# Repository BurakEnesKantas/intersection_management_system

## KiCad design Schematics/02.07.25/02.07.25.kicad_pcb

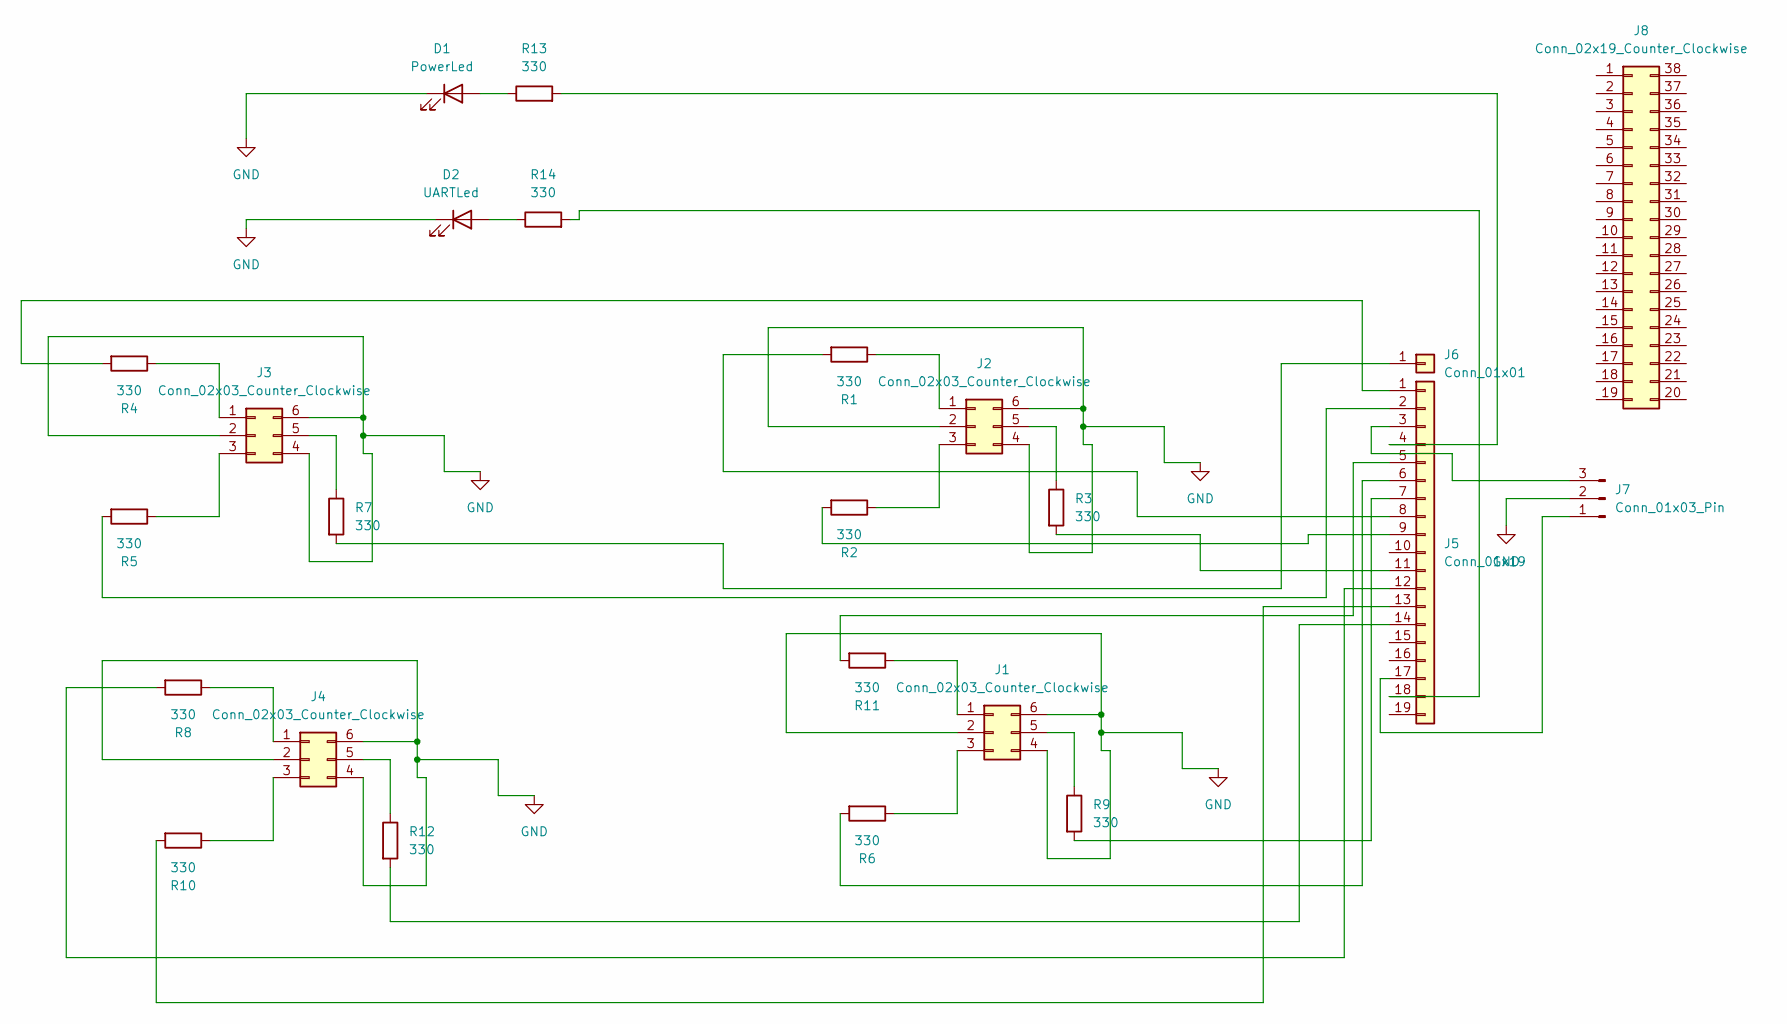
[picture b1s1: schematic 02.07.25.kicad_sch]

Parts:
D1: PowerLed; LED_D5.0mm
D2: UARTLed; LED_D5.0mm
J1, J2, J3, J4: Conn_02x03_Counter_Clockwise; PinSocket_2x03_P2.54mm_Vertical
J5: Conn_01x19; PinSocket_1x19_P2.54mm_Vertical
J6: Conn_01x01; PinSocket_1x01_P2.54mm_Vertical
J7: Conn_01x03_Pin; PinHeader_1x03_P2.54mm_Horizontal
J8: Conn_02x19_Counter_Clockwise; PinSocket_2x19_P2.54mm_Vertical
R1, R2, R3, R4, R5, R6, R7, R8, R9, R10, R11, R12, R13, R14: 330; R_Axial_DIN0207_L6.3mm_D2.5mm_P7.62mm_Horizontal

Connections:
GND: D1.1 (K), D2.1 (K), J1.2, J1.4, J1.6, J2.2, J2.4, J2.6, J3.2, J3.4, J3.6, J4.2, J4.4, J4.6, J7.2
unnamed: D1.2 (A), R13.1
unnamed: D2.2 (A), R14.1
unnamed: J1.1, R11.1
unnamed: J1.3, R6.1
unnamed: J1.5, R9.1
unnamed: J2.1, R1.1
unnamed: J2.3, R2.1
unnamed: J2.5, R3.1
unnamed: J3.1, R4.1
unnamed: J3.3, R5.1
unnamed: J3.5, R7.1
unnamed: J4.1, R8.1
unnamed: J4.3, R10.1
unnamed: J4.5, R12.1
unnamed: J5.1, R4.2
unnamed: J5.2, R5.2
unnamed: J5.3, J7.3
unnamed: J5.4, R13.2
unnamed: J5.5, R11.2
unnamed: J5.6, R6.2
unnamed: J5.7, R9.2
unnamed: J5.8, R1.2
unnamed: J5.9, R2.2
unnamed: J5.11, R3.2
unnamed: J5.12, R8.2
unnamed: J5.13, R10.2
unnamed: J5.14, R12.2
unnamed: J5.17, J7.1
unnamed: J5.18, R14.2
unnamed: J6.1, R7.2

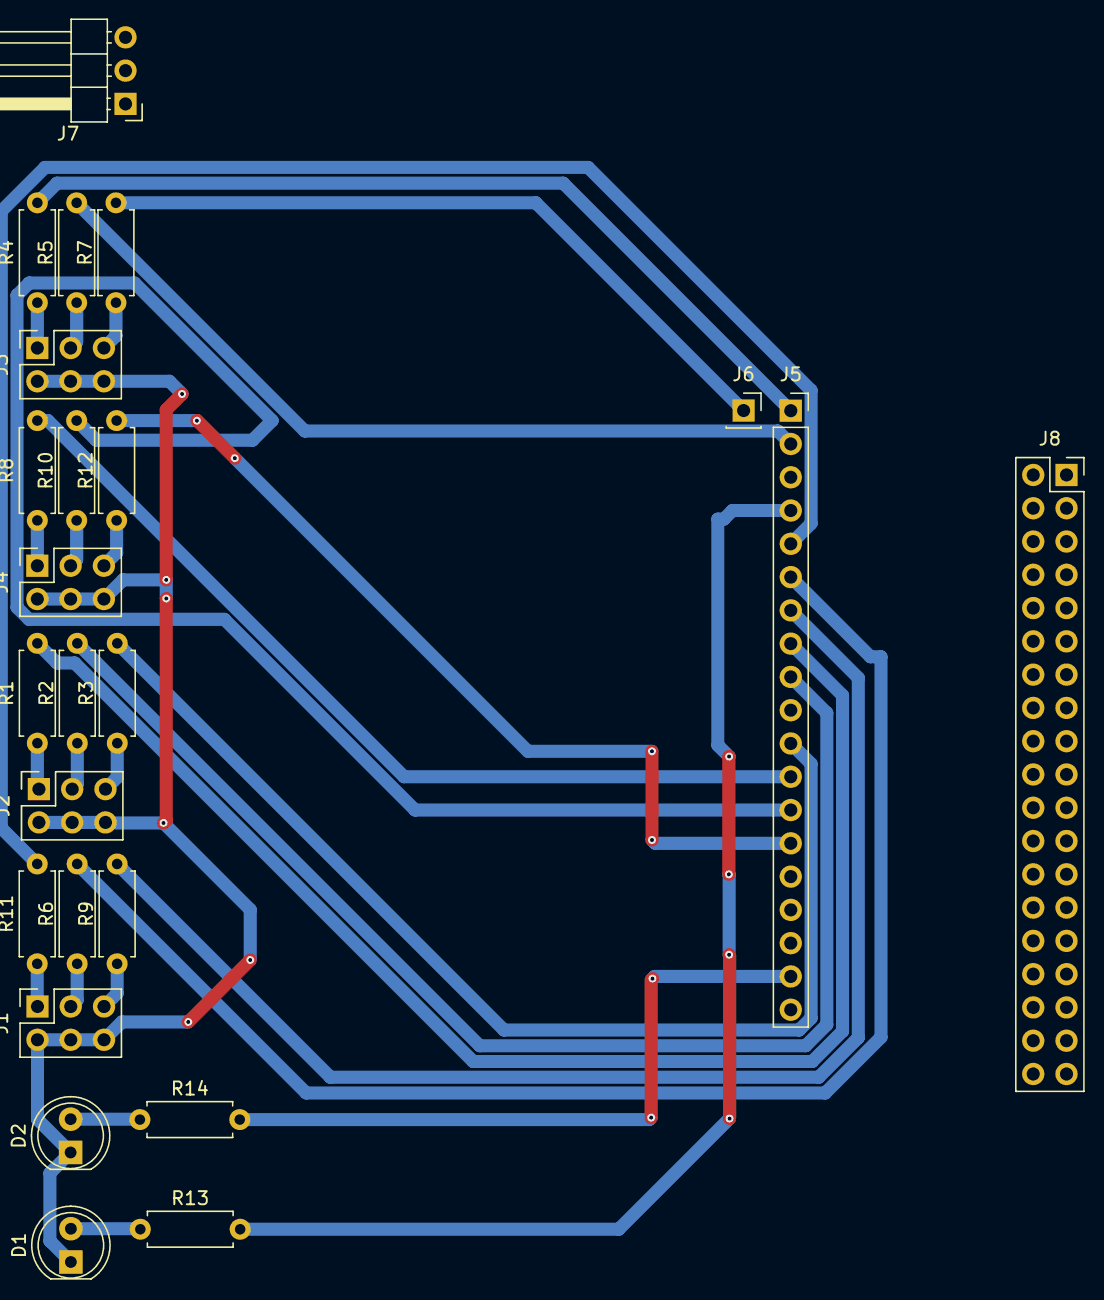
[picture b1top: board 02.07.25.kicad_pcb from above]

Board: 2 copper layers, 24 parts (0 on the bottom side), 31 nets.

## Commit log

2025-06-26 İlk yükleme
2025-06-29 versiyon güncelleme
2025-06-29 version update
2025-07-16 Add KiCad PCB and Schematic Files
2025-07-17 Update KiCad project files
2025-08-11 version update
